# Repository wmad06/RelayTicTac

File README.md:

# RelayTicTac
Relay logic Tic Tac Toe computer
bitfoot is coming!
POTATO!
I like to eat
LEMON!

potato + lemon = sour potato
sour + sweet = 0
sour potato + candy = potato
egg salad
This is a good use of the read me file

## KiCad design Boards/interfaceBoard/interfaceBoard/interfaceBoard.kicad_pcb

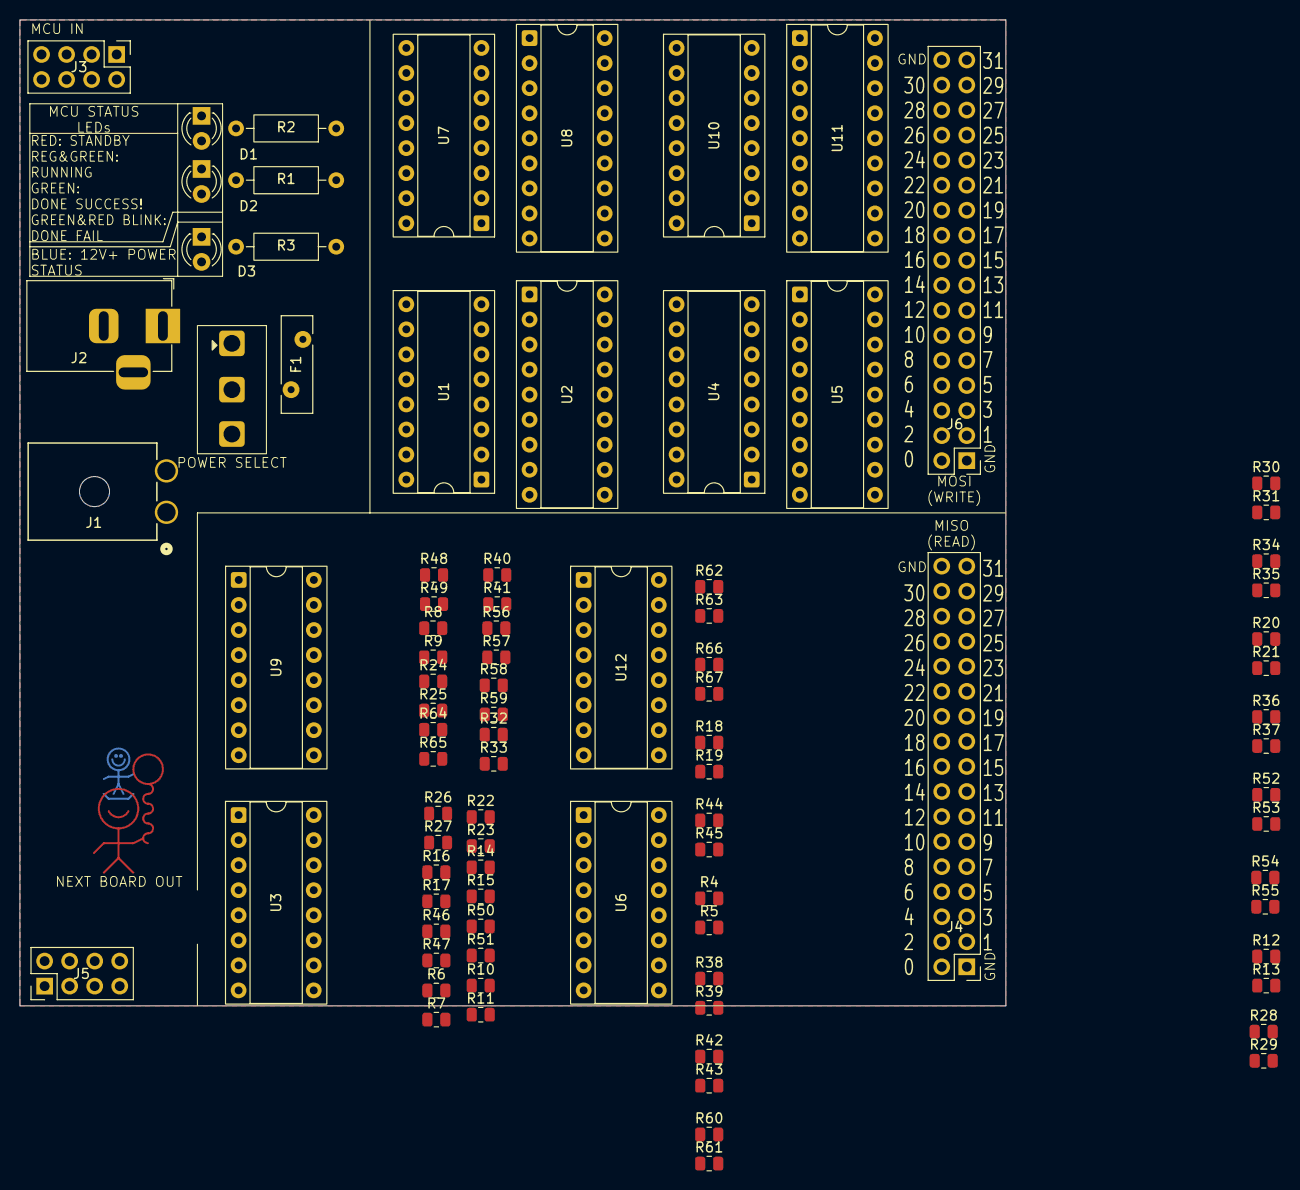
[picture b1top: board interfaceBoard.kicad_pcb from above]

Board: 2 copper layers, 100.0 x 100.0 mm, 90 parts (0 on the bottom side), 151 nets, no tracks yet.

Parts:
D1, D2, D3: LED; LED_D3.0mm
F1: Polyfuse; Fuse_Bourns_MF-RHT100
J1: 12V input (molex); CONN_SD-172648-0000_02_MOL
J2: Barrel_Jack_Switch; BarrelJack_Horizontal
J3: Interface With Arduino; PinHeader_2x04_P2.54mm_Vertical
J4, J6: Conn_02x17_Odd_Even; PinHeader_2x17_P2.54mm_Vertical
J5: DaisyCainOut; PinHeader_2x04_P2.54mm_Vertical
R1, R2: 2.2K; R_Axial_DIN0207_L6.3mm_D2.5mm_P10.16mm_Horizontal
R3: R; R_Axial_DIN0207_L6.3mm_D2.5mm_P10.16mm_Horizontal
R4, R6, R8, R10, R12, R14, R16, R18, R20, R22, R24, R26, R28, R30, R32, R34, R36, R38, R40, R42, R44, R46, R48, R50, R52, R54, R56, R58, R60, R62, R64, R66: 200K; R_0805_2012Metric
R5, R7, R9, R11, R13, R15, R17, R19, R21, R23, R25, R27, R29, R31, R33, R35, R37, R39, R41, R43, R45, R47, R49, R51, R53, R55, R57, R59, R61, R63, R65, R67: 100K; R_0805_2012Metric
SW1: SW_SPDT; SW_SPDT_SS-12D10L5
U1, U4, U7, U10: 74HC595; DIP-16_W7.62mm_Socket
U2, U5, U8, U11: TBD62783A; DIP-18_W7.62mm_Socket
U3, U6, U9, U12: 74HC165; DIP-16_W7.62mm_Socket

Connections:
5V+: J3.8, J5.8, R1.1, U1.10 (~SRCLR), U1.16 (VCC), U3.16 (VCC), U4.10 (~SRCLR), U4.16 (VCC), U6.16 (VCC), U7.10 (~SRCLR), U7.16 (VCC), U9.16 (VCC), U10.10 (~SRCLR), U10.16 (VCC), U12.16 (VCC)
12V+: F1.2, R3.1, U2.9 (VCC), U5.9 (VCC), U8.9 (VCC), U11.9 (VCC)
/MISO: J3.4, U3.9 (Q7)
/MISO_sheet1/D0: J4.10, R6.2, R7.1
/MISO_sheet1/D1: J4.11, R14.2, R15.1
/MISO_sheet1/D2: J4.12, R22.2, R23.1
/MISO_sheet1/D3: J4.13, R30.2, R31.1
/MISO_sheet1/D4: J4.14, R38.2, R39.1
/MISO_sheet1/D5: J4.15, R46.2, R47.1
/MISO_sheet1/D6: J4.16, R54.2, R55.1
/MISO_sheet1/D7: J4.17, R62.2, R63.1
/MISO_sheet1/SerIn: U6.10 (DS), U9.9 (Q7)
/MISO_sheet1/voltageDivider1/IN: R14.1, U6.12 (D1)
/MISO_sheet1/voltageDivider2/IN: R22.1, U6.13 (D2)
/MISO_sheet1/voltageDivider3/IN: R30.1, U6.14 (D3)
/MISO_sheet1/voltageDivider4/IN: R38.1, U6.3 (D4)
/MISO_sheet1/voltageDivider5/IN: R46.1, U6.4 (D5)
/MISO_sheet1/voltageDivider6/IN: R54.1, U6.5 (D6)
/MISO_sheet1/voltageDivider7/IN: R62.1, U6.6 (D7)
/MISO_sheet1/voltageDivider/IN: R6.1, U6.11 (D0)
/MISO_sheet2/D0: J4.18, R8.2, R9.1
/MISO_sheet2/D1: J4.19, R16.2, R17.1
/MISO_sheet2/D2: J4.20, R24.2, R25.1
/MISO_sheet2/D3: J4.21, R32.2, R33.1
/MISO_sheet2/D4: J4.22, R40.2, R41.1
/MISO_sheet2/D5: J4.23, R48.2, R49.1
/MISO_sheet2/D6: J4.24, R56.2, R57.1
/MISO_sheet2/D7: J4.25, R64.2, R65.1
/MISO_sheet2/SerIn: U9.10 (DS), U12.9 (Q7)
/MISO_sheet2/voltageDivider1/IN: R16.1, U9.12 (D1)
/MISO_sheet2/voltageDivider2/IN: R24.1, U9.13 (D2)
/MISO_sheet2/voltageDivider3/IN: R32.1, U9.14 (D3)
/MISO_sheet2/voltageDivider4/IN: R40.1, U9.3 (D4)
/MISO_sheet2/voltageDivider5/IN: R48.1, U9.4 (D5)
/MISO_sheet2/voltageDivider6/IN: R56.1, U9.5 (D6)
/MISO_sheet2/voltageDivider7/IN: R64.1, U9.6 (D7)
/MISO_sheet2/voltageDivider/IN: R8.1, U9.11 (D0)
/MISO_sheet3/D0: J4.26, R10.2, R11.1
/MISO_sheet3/D1: J4.27, R18.2, R19.1
/MISO_sheet3/D2: J4.28, R26.2, R27.1
/MISO_sheet3/D3: J4.29, R34.2, R35.1
/MISO_sheet3/D4: J4.30, R42.2, R43.1
/MISO_sheet3/D5: J4.31, R50.2, R51.1
/MISO_sheet3/D6: J4.32, R58.2, R59.1
/MISO_sheet3/D7: J4.33, R66.2, R67.1
/MISO_sheet3/SerIn: J5.4, U12.10 (DS)
/MISO_sheet3/voltageDivider1/IN: R18.1, U12.12 (D1)
/MISO_sheet3/voltageDivider2/IN: R26.1, U12.13 (D2)
/MISO_sheet3/voltageDivider3/IN: R34.1, U12.14 (D3)
/MISO_sheet3/voltageDivider4/IN: R42.1, U12.3 (D4)
/MISO_sheet3/voltageDivider5/IN: R50.1, U12.4 (D5)
/MISO_sheet3/voltageDivider6/IN: R58.1, U12.5 (D6)
/MISO_sheet3/voltageDivider7/IN: R66.1, U12.6 (D7)
/MISO_sheet3/voltageDivider/IN: R10.1, U12.11 (D0)
/MISO_sheet/D0: J4.2, R4.2, R5.1
/MISO_sheet/D1: J4.3, R12.2, R13.1
/MISO_sheet/D2: J4.4, R20.2, R21.1
/MISO_sheet/D3: J4.5, R28.2, R29.1
/MISO_sheet/D4: J4.6, R36.2, R37.1
/MISO_sheet/D5: J4.7, R44.2, R45.1
/MISO_sheet/D6: J4.8, R52.2, R53.1
/MISO_sheet/D7: J4.9, R60.2, R61.1
/MISO_sheet/SerIn: U3.10 (DS), U6.9 (Q7)
/MISO_sheet/voltageDivider1/IN: R12.1, U3.12 (D1)
/MISO_sheet/voltageDivider2/IN: R20.1, U3.13 (D2)
/MISO_sheet/voltageDivider3/IN: R28.1, U3.14 (D3)
/MISO_sheet/voltageDivider4/IN: R36.1, U3.3 (D4)
/MISO_sheet/voltageDivider5/IN: R44.1, U3.4 (D5)
/MISO_sheet/voltageDivider6/IN: R52.1, U3.5 (D6)
/MISO_sheet/voltageDivider7/IN: R60.1, U3.6 (D7)
/MISO_sheet/voltageDivider/IN: R4.1, U3.11 (D0)
/MOSI: J3.3, U1.14 (SER)
/MOSI_sheet1/O1: J6.10, U5.11 (O8)
/MOSI_sheet1/O2: J6.11, U5.12 (O7)
/MOSI_sheet1/O3: J6.12, U5.13 (O6)
/MOSI_sheet1/O4: J6.13, U5.14 (O5)
/MOSI_sheet1/O5: J6.14, U5.15 (O4)
/MOSI_sheet1/O6: J6.15, U5.16 (O3)
/MOSI_sheet1/O7: J6.16, U5.17 (O2)
/MOSI_sheet1/O8: J6.17, U5.18 (O1)
/MOSI_sheet1/QA: U4.15 (QA), U5.8 (I8)
/MOSI_sheet1/QB: U4.1 (QB), U5.7 (I7)
/MOSI_sheet1/QC: U4.2 (QC), U5.6 (I6)
/MOSI_sheet1/QD: U4.3 (QD), U5.5 (I5)
/MOSI_sheet1/QE: U4.4 (QE), U5.4 (I4)
/MOSI_sheet1/QF: U4.5 (QF), U5.3 (I3)
/MOSI_sheet1/QG: U4.6 (QG), U5.2 (I2)
/MOSI_sheet1/QH: U4.7 (QH), U5.1 (I1)
/MOSI_sheet1/QH': U4.9 (QH'), U7.14 (SER)
/MOSI_sheet2/O1: J6.18, U8.11 (O8)
/MOSI_sheet2/O2: J6.19, U8.12 (O7)
/MOSI_sheet2/O3: J6.20, U8.13 (O6)
/MOSI_sheet2/O4: J6.21, U8.14 (O5)
/MOSI_sheet2/O5: J6.22, U8.15 (O4)
/MOSI_sheet2/O6: J6.23, U8.16 (O3)
/MOSI_sheet2/O7: J6.24, U8.17 (O2)
/MOSI_sheet2/O8: J6.25, U8.18 (O1)
/MOSI_sheet2/QA: U7.15 (QA), U8.8 (I8)
/MOSI_sheet2/QB: U7.1 (QB), U8.7 (I7)
/MOSI_sheet2/QC: U7.2 (QC), U8.6 (I6)
/MOSI_sheet2/QD: U7.3 (QD), U8.5 (I5)
/MOSI_sheet2/QE: U7.4 (QE), U8.4 (I4)
/MOSI_sheet2/QF: U7.5 (QF), U8.3 (I3)
/MOSI_sheet2/QG: U7.6 (QG), U8.2 (I2)
/MOSI_sheet2/QH: U7.7 (QH), U8.1 (I1)
/MOSI_sheet2/QH': U7.9 (QH'), U10.14 (SER)
/MOSI_sheet3/O1: J6.26, U11.11 (O8)
/MOSI_sheet3/O2: J6.27, U11.12 (O7)
/MOSI_sheet3/O3: J6.28, U11.13 (O6)
/MOSI_sheet3/O4: J6.29, U11.14 (O5)
/MOSI_sheet3/O5: J6.30, U11.15 (O4)
/MOSI_sheet3/O6: J6.31, U11.16 (O3)
/MOSI_sheet3/O7: J6.32, U11.17 (O2)
/MOSI_sheet3/O8: J6.33, U11.18 (O1)
/MOSI_sheet3/QA: U10.15 (QA), U11.8 (I8)
/MOSI_sheet3/QB: U10.1 (QB), U11.7 (I7)
/MOSI_sheet3/QC: U10.2 (QC), U11.6 (I6)
/MOSI_sheet3/QD: U10.3 (QD), U11.5 (I5)
/MOSI_sheet3/QE: U10.4 (QE), U11.4 (I4)
/MOSI_sheet3/QF: U10.5 (QF), U11.3 (I3)
/MOSI_sheet3/QG: U10.6 (QG), U11.2 (I2)
/MOSI_sheet3/QH: U10.7 (QH), U11.1 (I1)
/MOSI_sheet3/QH': J5.3, U10.9 (QH')
/MOSI_sheet/O1: J6.2, U2.11 (O8)
/MOSI_sheet/O2: J6.3, U2.12 (O7)
/MOSI_sheet/O3: J6.4, U2.13 (O6)
/MOSI_sheet/O4: J6.5, U2.14 (O5)
/MOSI_sheet/O5: J6.6, U2.15 (O4)
/MOSI_sheet/O6: J6.7, U2.16 (O3)
/MOSI_sheet/O7: J6.8, U2.17 (O2)
/MOSI_sheet/O8: J6.9, U2.18 (O1)
/MOSI_sheet/QA: U1.15 (QA), U2.8 (I8)
/MOSI_sheet/QB: U1.1 (QB), U2.7 (I7)
/MOSI_sheet/QC: U1.2 (QC), U2.6 (I6)
/MOSI_sheet/QD: U1.3 (QD), U2.5 (I5)
/MOSI_sheet/QE: U1.4 (QE), U2.4 (I4)
/MOSI_sheet/QF: U1.5 (QF), U2.3 (I3)
/MOSI_sheet/QG: U1.6 (QG), U2.2 (I2)
/MOSI_sheet/QH: U1.7 (QH), U2.1 (I1)
/MOSI_sheet/QH': U1.9 (QH'), U4.14 (SER)
/STATUS: D1.1 (K), J3.7, J5.7, R2.1
CLK: J3.2, J5.2, U1.11 (SRCLK), U3.2 (CP), U4.11 (SRCLK), U6.2 (CP), U7.11 (SRCLK), U9.2 (CP), U10.11 (SRCLK), U12.2 (CP)
GND: D2.1 (K), D3.1 (K), J1.1, J2.2, J2.3, J3.1, J4.1, J4.34, J5.1, J6.1, J6.34, R5.2, R7.2, R9.2, R11.2, R13.2, R15.2, R17.2, R19.2, R21.2, R23.2, R25.2, R27.2, R29.2, R31.2, R33.2, R35.2, R37.2, R39.2, R41.2, R43.2, R45.2, R47.2, R49.2, R51.2, R53.2, R55.2, R57.2, R59.2, R61.2, R63.2, R65.2, R67.2, U1.8 (GND), U1.13 (~OE), U2.10 (GND), U3.8 (GND), U3.15 (~CE), U4.8 (GND), U4.13 (~OE), U5.10 (GND), U6.8 (GND), U6.15 (~CE), U7.8 (GND), U7.13 (~OE), U8.10 (GND), U9.8 (GND), U9.15 (~CE), U10.8 (GND), U10.13 (~OE), U11.10 (GND), U12.8 (GND), U12.15 (~CE)
LATCH: J3.5, J5.5, U1.12 (RCLK), U4.12 (RCLK), U7.12 (RCLK), U10.12 (RCLK)
LOAD: J3.6, J5.6, U3.1 (~PL), U6.1 (~PL), U9.1 (~PL), U12.1 (~PL)
unnamed: D1.2 (A), R1.2
unnamed: D2.2 (A), R2.2
unnamed: D3.2 (A), R3.2
unnamed: J1.2, SW1.3 (C)
unnamed: J2.1, SW1.1 (A)
unnamed: F1.1, SW1.2 (B)

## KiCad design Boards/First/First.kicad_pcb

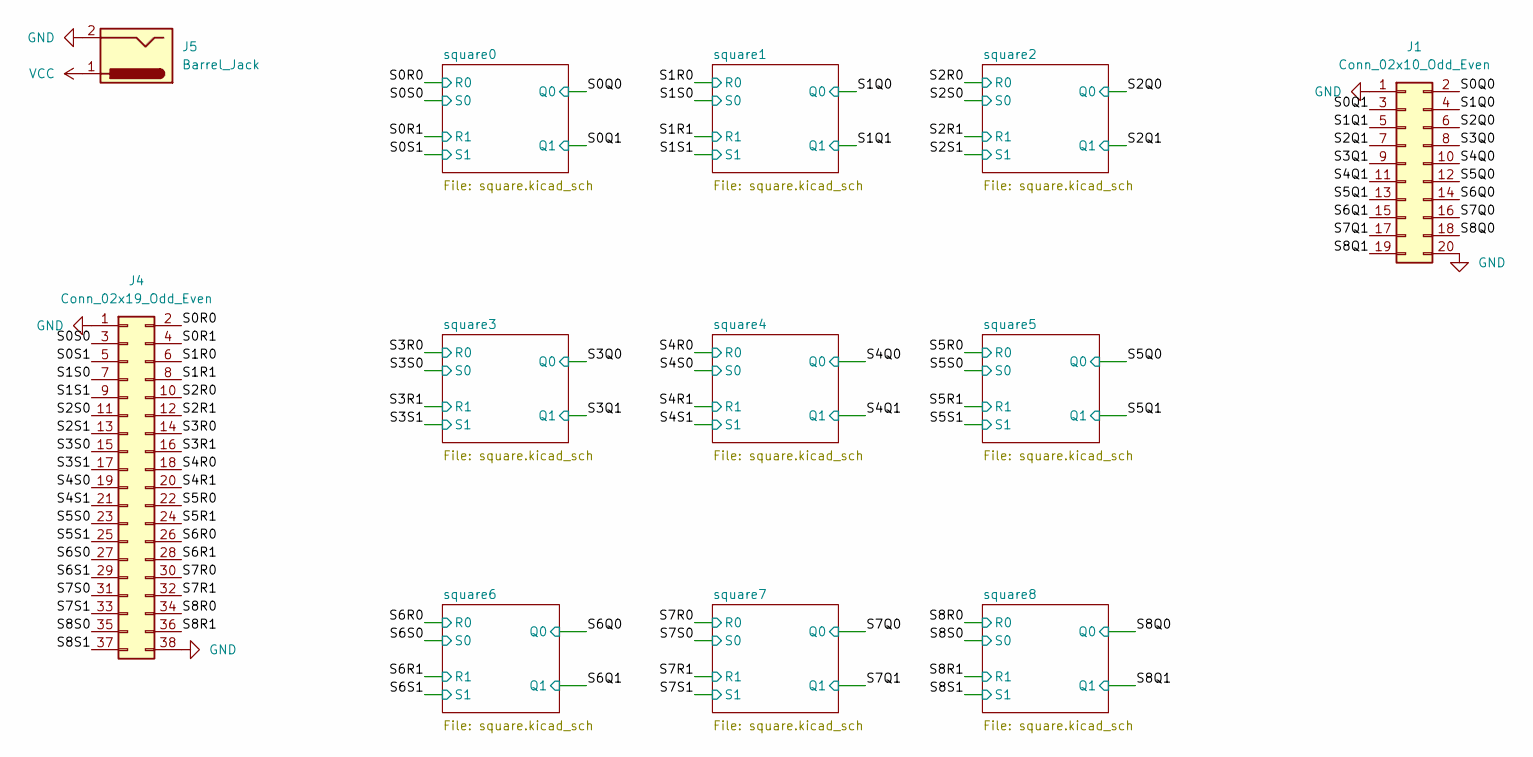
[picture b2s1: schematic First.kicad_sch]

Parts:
J1: Conn_02x10_Odd_Even; IDC-Header_2x10_P2.54mm_Latch_Vertical
J4: Conn_02x19_Odd_Even; PinHeader_2x19_P2.54mm_Vertical
J5: Barrel_Jack; BarrelJack_Horizontal

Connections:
/S0Q0: J1.2; also elsewhere on the board
/S0Q1: J1.3; also elsewhere on the board
/S0R0: J4.2; also elsewhere on the board
/S0R1: J4.4; also elsewhere on the board
/S0S0: J4.3; also elsewhere on the board
/S0S1: J4.5; also elsewhere on the board
/S1Q0: J1.4; also elsewhere on the board
/S1Q1: J1.5; also elsewhere on the board
/S1R0: J4.6; also elsewhere on the board
/S1R1: J4.8; also elsewhere on the board
/S1S0: J4.7; also elsewhere on the board
/S1S1: J4.9; also elsewhere on the board
/S2Q0: J1.6; also elsewhere on the board
/S2Q1: J1.7; also elsewhere on the board
/S2R0: J4.10; also elsewhere on the board
/S2R1: J4.12; also elsewhere on the board
/S2S0: J4.11; also elsewhere on the board
/S2S1: J4.13; also elsewhere on the board
/S3Q0: J1.8; also elsewhere on the board
/S3Q1: J1.9; also elsewhere on the board
/S3R0: J4.14; also elsewhere on the board
/S3R1: J4.16; also elsewhere on the board
/S3S0: J4.15; also elsewhere on the board
/S3S1: J4.17; also elsewhere on the board
/S4Q0: J1.10; also elsewhere on the board
/S4Q1: J1.11; also elsewhere on the board
/S4R0: J4.18; also elsewhere on the board
/S4R1: J4.20; also elsewhere on the board
/S4S0: J4.19; also elsewhere on the board
/S4S1: J4.21; also elsewhere on the board
/S5Q0: J1.12; also elsewhere on the board
/S5Q1: J1.13; also elsewhere on the board
/S5R0: J4.22; also elsewhere on the board
/S5R1: J4.24; also elsewhere on the board
/S5S0: J4.23; also elsewhere on the board
/S5S1: J4.25; also elsewhere on the board
/S6Q0: J1.14; also elsewhere on the board
/S6Q1: J1.15; also elsewhere on the board
/S6R0: J4.26; also elsewhere on the board
/S6R1: J4.28; also elsewhere on the board
/S6S0: J4.27; also elsewhere on the board
/S6S1: J4.29; also elsewhere on the board
/S7Q0: J1.16; also elsewhere on the board
/S7Q1: J1.17; also elsewhere on the board
/S7R0: J4.30; also elsewhere on the board
/S7R1: J4.32; also elsewhere on the board
/S7S0: J4.31; also elsewhere on the board
/S7S1: J4.33; also elsewhere on the board
/S8Q0: J1.18; also elsewhere on the board
/S8Q1: J1.19; also elsewhere on the board
/S8R0: J4.34; also elsewhere on the board
/S8R1: J4.36; also elsewhere on the board
/S8S0: J4.35; also elsewhere on the board
/S8S1: J4.37; also elsewhere on the board
GND: J1.1, J1.20, J4.1, J4.38, J5.2; also elsewhere on the board
VCC: J5.1; also elsewhere on the board

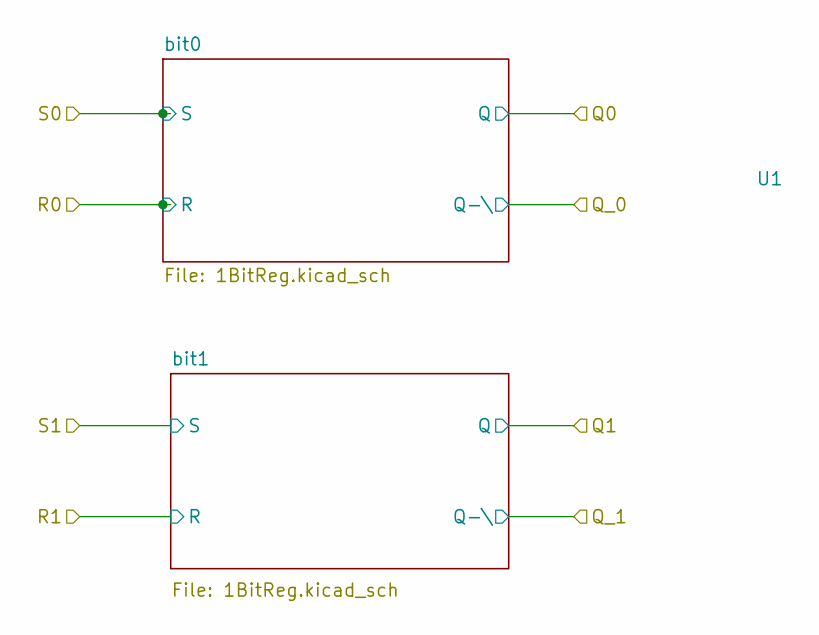
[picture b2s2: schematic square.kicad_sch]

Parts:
U1: squareRegOutSilk

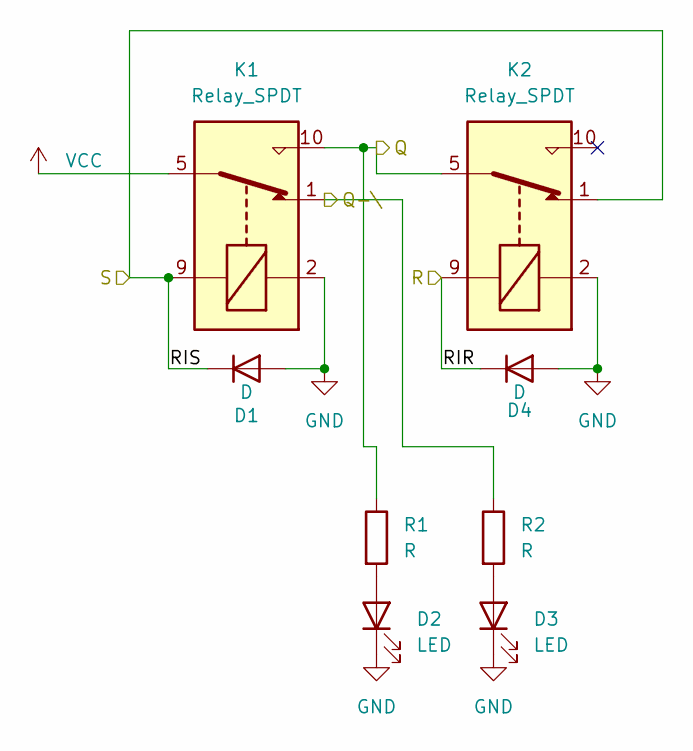
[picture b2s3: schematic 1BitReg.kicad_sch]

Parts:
D1, D4: D; D_DO-35_SOD27_P7.62mm_Horizontal
D2, D3: LED; LED_D3.0mm
K1, K2: Relay_SPDT; Relay_SPDT_Omron_G5V-1
R1, R2: R; R_Axial_DIN0207_L6.3mm_D2.5mm_P7.62mm_Horizontal

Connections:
/S0Q0: K1.10, K2.5, K2.6, R1.1; also elsewhere on the board
/S0R0: D4.1 (K), K2.9; also elsewhere on the board
/S0S0: D1.1 (K), K1.9, K2.1; also elsewhere on the board
/square0/Q_0: K1.1, R2.1
GND: D1.2 (A), D2.1 (K), D3.1 (K), D4.2 (A), K1.2, K2.2; also elsewhere on the board
unnamed: D2.2 (A), R1.2
unnamed: D3.2 (A), R2.2
VCC: K1.5, K1.6; also elsewhere on the board

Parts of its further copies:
D5, D8, D9, D12, D13, D16, D17, D20, D21, D24, D25, D28, D29, D32, D33, D36, D37, D40, D41, D44, D45, D48, D49, D52, D53, D56, D57, D60, D61, D64, D65, D68, D69, D72: D; D_DO-35_SOD27_P7.62mm_Horizontal
D6, D7, D10, D11, D14, D15, D18, D19, D22, D23, D26, D27, D30, D31, D34, D35, D38, D39, D42, D43, D46, D47, D50, D51, D54, D55, D58, D59, D62, D63, D66, D67, D70, D71: LED; LED_D3.0mm
K3, K4, K5, K6, K7, K8, K9, K10, K11, K12, K13, K14, K15, K16, K17, K18, K19, K20, K21, K22, K23, K24, K25, K26, K27, K28, K29, K30, K31, K32, K33, K34, K35, K36: Relay_SPDT; Relay_SPDT_Omron_G5V-1
R3, R4, R5, R6, R7, R8, R9, R10, R11, R12, R13, R14, R15, R16, R17, R18, R19, R20, R21, R22, R23, R24, R25, R26, R27, R28, R29, R30, R31, R32, R33, R34, R35, R36: R; R_Axial_DIN0207_L6.3mm_D2.5mm_P7.62mm_Horizontal

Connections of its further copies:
/S0Q1: K3.10, K4.5, K4.6, R3.1; also elsewhere on the board
/S0R1: D8.1 (K), K4.9; also elsewhere on the board
/S0S1: D5.1 (K), K3.9, K4.1; also elsewhere on the board
/S1Q0: K5.10, K6.5, K6.6, R5.1; also elsewhere on the board
/S1Q1: K7.10, K8.5, K8.6, R7.1; also elsewhere on the board
/S1R0: D12.1 (K), K6.9; also elsewhere on the board
/S1R1: D16.1 (K), K8.9; also elsewhere on the board
/S1S0: D9.1 (K), K5.9, K6.1; also elsewhere on the board
/S1S1: D13.1 (K), K7.9, K8.1; also elsewhere on the board
/S2Q0: K9.10, K10.5, K10.6, R9.1; also elsewhere on the board
/S2Q1: K11.10, K12.5, K12.6, R11.1; also elsewhere on the board
/S2R0: D20.1 (K), K10.9; also elsewhere on the board
/S2R1: D24.1 (K), K12.9; also elsewhere on the board
/S2S0: D17.1 (K), K9.9, K10.1; also elsewhere on the board
/S2S1: D21.1 (K), K11.9, K12.1; also elsewhere on the board
/S3Q0: K13.10, K14.5, K14.6, R13.1; also elsewhere on the board
/S3Q1: K15.10, K16.5, K16.6, R15.1; also elsewhere on the board
/S3R0: D28.1 (K), K14.9; also elsewhere on the board
/S3R1: D32.1 (K), K16.9; also elsewhere on the board
/S3S0: D25.1 (K), K13.9, K14.1; also elsewhere on the board
/S3S1: D29.1 (K), K15.9, K16.1; also elsewhere on the board
/S4Q0: K17.10, K18.5, K18.6, R17.1; also elsewhere on the board
/S4Q1: K19.10, K20.5, K20.6, R19.1; also elsewhere on the board
/S4R0: D36.1 (K), K18.9; also elsewhere on the board
/S4R1: D40.1 (K), K20.9; also elsewhere on the board
/S4S0: D33.1 (K), K17.9, K18.1; also elsewhere on the board
/S4S1: D37.1 (K), K19.9, K20.1; also elsewhere on the board
/S5Q0: K21.10, K22.5, K22.6, R21.1; also elsewhere on the board
/S5Q1: K23.10, K24.5, K24.6, R23.1; also elsewhere on the board
/S5R0: D44.1 (K), K22.9; also elsewhere on the board
/S5R1: D48.1 (K), K24.9; also elsewhere on the board
/S5S0: D41.1 (K), K21.9, K22.1; also elsewhere on the board
/S5S1: D45.1 (K), K23.9, K24.1; also elsewhere on the board
/S6Q0: K25.10, K26.5, K26.6, R25.1; also elsewhere on the board
/S6Q1: K27.10, K28.5, K28.6, R27.1; also elsewhere on the board
/S6R0: D52.1 (K), K26.9; also elsewhere on the board
/S6R1: D56.1 (K), K28.9; also elsewhere on the board
/S6S0: D49.1 (K), K25.9, K26.1; also elsewhere on the board
/S6S1: D53.1 (K), K27.9, K28.1; also elsewhere on the board
/S7Q0: K29.10, K30.5, K30.6, R29.1; also elsewhere on the board
/S7Q1: K31.10, K32.5, K32.6, R31.1; also elsewhere on the board
/S7R0: D60.1 (K), K30.9; also elsewhere on the board
/S7R1: D64.1 (K), K32.9; also elsewhere on the board
/S7S0: D57.1 (K), K29.9, K30.1; also elsewhere on the board
/S7S1: D61.1 (K), K31.9, K32.1; also elsewhere on the board
/S8Q0: K33.10, K34.5, K34.6, R33.1; also elsewhere on the board
/S8Q1: K35.10, K36.5, K36.6, R35.1; also elsewhere on the board
/S8R0: D68.1 (K), K34.9; also elsewhere on the board
/S8R1: D72.1 (K), K36.9; also elsewhere on the board
/S8S0: D65.1 (K), K33.9, K34.1; also elsewhere on the board
/S8S1: D69.1 (K), K35.9, K36.1; also elsewhere on the board
/square0/Q_1: K3.1, R4.1
/square1/Q_0: K5.1, R6.1
/square1/Q_1: K7.1, R8.1
/square2/Q_0: K9.1, R10.1
/square2/Q_1: K11.1, R12.1
/square3/Q_0: K13.1, R14.1
/square3/Q_1: K15.1, R16.1
/square4/Q_0: K17.1, R18.1
/square4/Q_1: K19.1, R20.1
/square5/Q_0: K21.1, R22.1
/square5/Q_1: K23.1, R24.1
/square6/Q_0: K25.1, R26.1
/square6/Q_1: K27.1, R28.1
/square7/Q_0: K29.1, R30.1
/square7/Q_1: K31.1, R32.1
/square8/Q_0: K33.1, R34.1
/square8/Q_1: K35.1, R36.1
GND: D5.2 (A), D6.1 (K), D7.1 (K), D8.2 (A), D9.2 (A), D10.1 (K), D11.1 (K), D12.2 (A), D13.2 (A), D14.1 (K), D15.1 (K), D16.2 (A), D17.2 (A), D18.1 (K), D19.1 (K), D20.2 (A), D21.2 (A), D22.1 (K), D23.1 (K), D24.2 (A), D25.2 (A), D26.1 (K), D27.1 (K), D28.2 (A), D29.2 (A), D30.1 (K), D31.1 (K), D32.2 (A), D33.2 (A), D34.1 (K), D35.1 (K), D36.2 (A), D37.2 (A), D38.1 (K), D39.1 (K), D40.2 (A), D41.2 (A), D42.1 (K), D43.1 (K), D44.2 (A), D45.2 (A), D46.1 (K), D47.1 (K), D48.2 (A), D49.2 (A), D50.1 (K), D51.1 (K), D52.2 (A), D53.2 (A), D54.1 (K), D55.1 (K), D56.2 (A), D57.2 (A), D58.1 (K), D59.1 (K), D60.2 (A), D61.2 (A), D62.1 (K), D63.1 (K), D64.2 (A), D65.2 (A), D66.1 (K), D67.1 (K), D68.2 (A), D69.2 (A), D70.1 (K), D71.1 (K), D72.2 (A), K3.2, K4.2, K5.2, K6.2, K7.2, K8.2, K9.2, K10.2, K11.2, K12.2, K13.2, K14.2, K15.2, K16.2, K17.2, K18.2, K19.2, K20.2, K21.2, K22.2, K23.2, K24.2, K25.2, K26.2, K27.2, K28.2, K29.2, K30.2, K31.2, K32.2, K33.2, K34.2, K35.2, K36.2; also elsewhere on the board
unnamed: D6.2 (A), R3.2
unnamed: D7.2 (A), R4.2
unnamed: D10.2 (A), R5.2
unnamed: D11.2 (A), R6.2
unnamed: D14.2 (A), R7.2
unnamed: D15.2 (A), R8.2
unnamed: D18.2 (A), R9.2
unnamed: D19.2 (A), R10.2
unnamed: D22.2 (A), R11.2
unnamed: D23.2 (A), R12.2
unnamed: D26.2 (A), R13.2
unnamed: D27.2 (A), R14.2
unnamed: D30.2 (A), R15.2
unnamed: D31.2 (A), R16.2
unnamed: D34.2 (A), R17.2
unnamed: D35.2 (A), R18.2
unnamed: D38.2 (A), R19.2
unnamed: D39.2 (A), R20.2
unnamed: D42.2 (A), R21.2
unnamed: D43.2 (A), R22.2
unnamed: D46.2 (A), R23.2
unnamed: D47.2 (A), R24.2
unnamed: D50.2 (A), R25.2
unnamed: D51.2 (A), R26.2
unnamed: D54.2 (A), R27.2
unnamed: D55.2 (A), R28.2
unnamed: D58.2 (A), R29.2
unnamed: D59.2 (A), R30.2
unnamed: D62.2 (A), R31.2
unnamed: D63.2 (A), R32.2
unnamed: D66.2 (A), R33.2
unnamed: D67.2 (A), R34.2
unnamed: D70.2 (A), R35.2
unnamed: D71.2 (A), R36.2
VCC: K3.5, K3.6, K5.5, K5.6, K7.5, K7.6, K9.5, K9.6, K11.5, K11.6, K13.5, K13.6, K15.5, K15.6, K17.5, K17.6, K19.5, K19.6, K21.5, K21.6, K23.5, K23.6, K25.5, K25.6, K27.5, K27.6, K29.5, K29.6, K31.5, K31.6, K33.5, K33.6, K35.5, K35.6; also elsewhere on the board

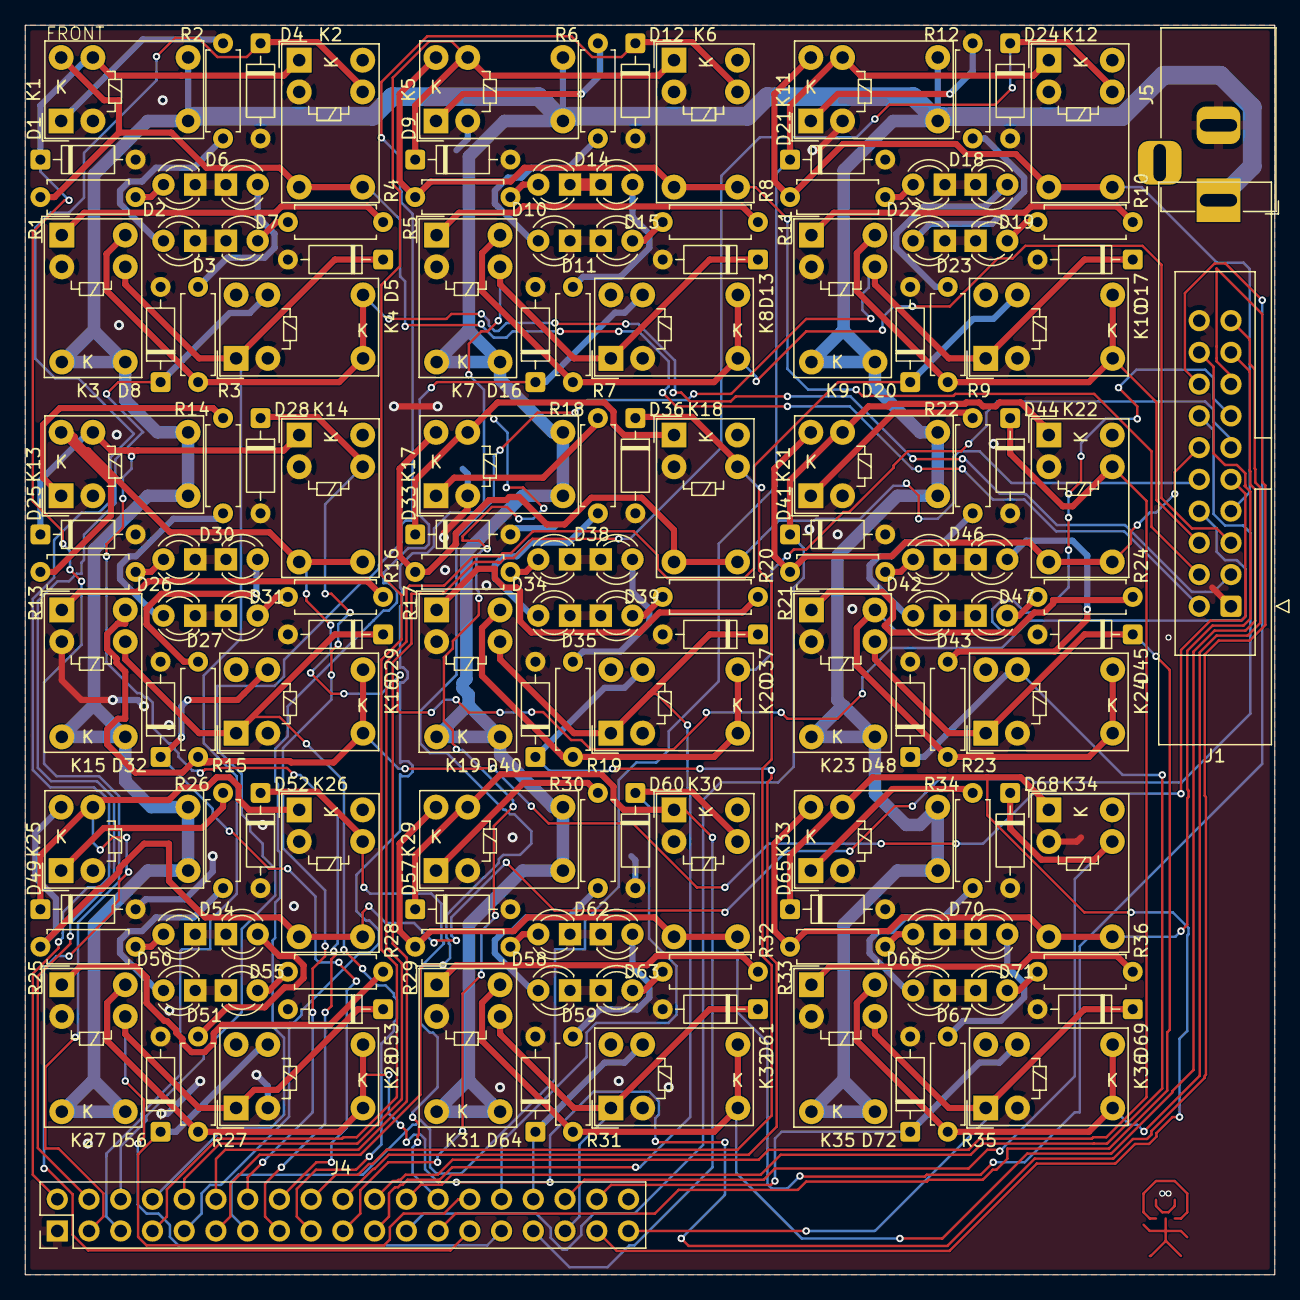
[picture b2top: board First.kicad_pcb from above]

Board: 2 copper layers, 100.0 x 100.0 mm, 148 parts (0 on the bottom side), 110 nets.

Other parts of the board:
U7: squareRegOutSilk
